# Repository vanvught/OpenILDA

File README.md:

---> WORK IN PROGRESS <---

OpenILDA
========

Cheap ILDA SPI DAC board for Raspberry Pi. 

ILDA output: balanced X/Y - 12 bit,  balanced R/G/B/I - 8 bit.

Playback of ILDA files from external SD card.

OSC support (using RPi <- UART/USB -> PC[java] <- UDP-> iPad/iPod)

This OpenILDA DAC board uses the SPI interface for controlling 3 DAC's. The MCP49x2 device is a dual channel DAC.
As the RPi just has 2 SPI chip enable lines, the DAC /CS lines are created by using a HC139 See viewtopic.php?p=333992#p333992

Of course, I could have used a 12-bit 8-channel DAC (for example TLV5610IDW). This would create less components. However, such a DAC is relatively expensive (24 Euro) and it would have a SO-20 package.

I will post the OpenILDA sd-card player with OSC support (written for bare-metal) soon.

What's next? ()
*. Reduce the amount of OPAMP's (from 6 to 3)
*. Enable using single voltage power supply
	- Use DC/DC converter for -12 volt / +12 volt
	- Use 7805 for 5 volt output voltage
	
See also http://www.raspberrypi.org/phpBB3/viewtopic.php?p=366647#p366647

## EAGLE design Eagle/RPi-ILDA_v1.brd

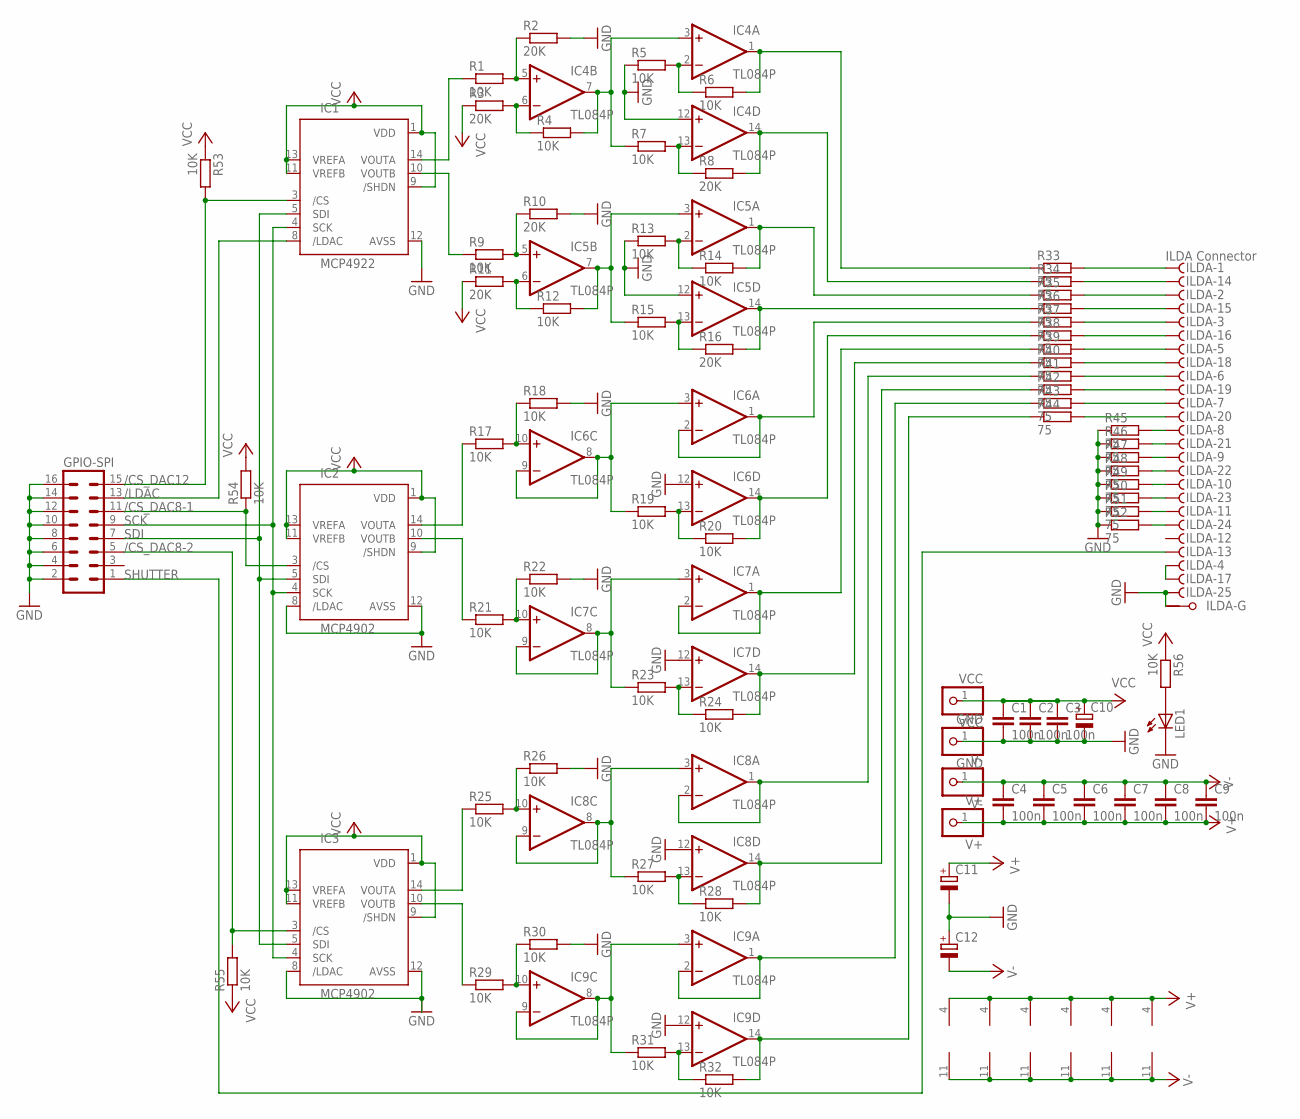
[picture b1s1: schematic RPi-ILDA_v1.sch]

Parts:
C1, C2, C3, C4, C5, C6, C7, C8, C9: 100n; C050-024X044
C10, C11, C12: CPOL-EUE5-6; E5-6
GND: GND; 1X01
GPIO-SPI: MA08-2
IC1: MCP4922; DIL14
IC2, IC3: MCP4902; DIL14
IC4, IC5, IC6, IC7, IC8, IC9: TL084P; DIL14
ILDA: ILDA Connector; F25HP
LED1: LED3MM
R1, R7, R9, R15, R17, R21, R22, R25, R29, R30, R53, R54, R55: 10K; 0204/5
R2, R8, R10, R16: 20K; 0204V
R3, R11: 20K; 0204/5
R4, R5, R6, R12, R13, R14, R18, R19, R20, R23, R24, R26, R27, R28, R31, R32, R56: 10K; 0204V
R33, R34, R35, R36, R37, R38, R39, R40, R41, R42, R43, R44, R45, R46, R47, R48, R49, R50, R51, R52: 75; 0204V
V+: V+; 1X01
V-: V-; 1X01
VCC: VCC; 1X01

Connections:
/CS_DAC8-1: GPIO-SPI.11, IC2.3 (/CS), R54.1
/CS_DAC8-2: GPIO-SPI.5, IC3.3 (/CS), R55.2
/CS_DAC12: GPIO-SPI.15, IC1.3 (/CS), R53.2
/LDAC: GPIO-SPI.13, IC1.8 (/LDAC)
GND: C1.2, C2.2, C3.2, C10.-, C11.-, C12.+, GND.1, GPIO-SPI.2, GPIO-SPI.4, GPIO-SPI.6, GPIO-SPI.8, GPIO-SPI.10, GPIO-SPI.12, GPIO-SPI.14, GPIO-SPI.16, IC1.12 (AVSS), IC2.8 (/LDAC), IC2.12 (AVSS), IC3.8 (/LDAC), IC3.12 (AVSS), IC4.12 (+IN), IC5.12 (+IN), IC6.12 (+IN), IC7.12 (+IN), IC8.12 (+IN), IC9.12 (+IN), ILDA.25 (F), ILDA.G1, LED1.K (C), R2.2, R5.1, R10.2, R13.1, R18.2, R22.2, R26.2, R30.2, R45.1, R46.1, R47.1, R48.1, R49.1, R50.1, R51.1, R52.1
unnamed: LED1.A, R56.2
unnamed: ILDA.3 (F), R37.2
unnamed: IC4.2 (-IN), R5.2, R6.1
unnamed: IC5.2 (-IN), R13.2, R14.1
unnamed: IC5.13 (-IN), R15.2, R16.1
unnamed: IC3.14 (VOUTA), R25.1
unnamed: IC7.14 (OUT), R24.2, R40.1
unnamed: IC7.13 (-IN), R23.2, R24.1
unnamed: IC7.10 (+IN), R21.2, R22.1
unnamed: ILDA.4 (F), ILDA.17 (F)
unnamed: IC7.3 (+IN), IC7.8 (OUT), IC7.9 (-IN), R23.1
unnamed: IC7.1 (OUT), IC7.2 (-IN), R39.1
unnamed: ILDA.5 (F), R39.2
unnamed: IC1.14 (VOUTA), R1.1
unnamed: IC1.10 (VOUTB), R9.1
unnamed: ILDA.18 (F), R40.2
unnamed: IC6.14 (OUT), R20.2, R38.1
unnamed: IC4.13 (-IN), R7.2, R8.1
unnamed: IC6.13 (-IN), R19.2, R20.1
unnamed: IC8.14 (OUT), R28.2, R42.1
unnamed: IC6.10 (+IN), R17.2, R18.1
unnamed: IC6.3 (+IN), IC6.8 (OUT), IC6.9 (-IN), R19.1
unnamed: IC6.1 (OUT), IC6.2 (-IN), R37.1
unnamed: IC8.13 (-IN), R27.2, R28.1
unnamed: IC8.10 (+IN), R25.2, R26.1
unnamed: IC8.3 (+IN), IC8.8 (OUT), IC8.9 (-IN), R27.1
unnamed: IC8.1 (OUT), IC8.2 (-IN), R41.1
unnamed: ILDA.8 (F), R45.2
unnamed: ILDA.6 (F), R41.2
unnamed: ILDA.16 (F), R38.2
unnamed: IC5.14 (OUT), R16.2, R36.1
unnamed: ILDA.19 (F), R42.2
unnamed: IC5.1 (OUT), R14.2, R35.1
unnamed: IC9.14 (OUT), R32.2, R44.1
unnamed: IC9.13 (-IN), R31.2, R32.1
unnamed: IC9.10 (+IN), R29.2, R30.1
unnamed: IC9.3 (+IN), IC9.8 (OUT), IC9.9 (-IN), R31.1
unnamed: IC9.1 (OUT), IC9.2 (-IN), R43.1
unnamed: IC3.10 (VOUTB), R29.1
unnamed: IC4.14 (OUT), R8.2, R34.1
unnamed: IC4.1 (OUT), R6.2, R33.1
unnamed: IC5.3 (+IN), IC5.7 (OUT), R12.2, R15.1
unnamed: IC4.6 (-IN), R3.2, R4.1
unnamed: IC5.6 (-IN), R11.2, R12.1
unnamed: ILDA.7 (F), R43.2
unnamed: ILDA.20 (F), R44.2
unnamed: ILDA.21 (F), R46.2
unnamed: ILDA.9 (F), R47.2
unnamed: ILDA.22 (F), R48.2
unnamed: ILDA.10 (F), R49.2
unnamed: ILDA.23 (F), R50.2
unnamed: IC2.14 (VOUTA), R17.1
unnamed: ILDA.11 (F), R51.2
unnamed: ILDA.24 (F), R52.2
unnamed: IC2.10 (VOUTB), R21.1
unnamed: IC5.5 (+IN), R9.2, R10.1
unnamed: IC4.5 (+IN), R1.2, R2.1
unnamed: IC4.3 (+IN), IC4.7 (OUT), R4.2, R7.1
unnamed: ILDA.1 (F), R33.2
unnamed: ILDA.14 (F), R34.2
unnamed: ILDA.15 (F), R36.2
unnamed: ILDA.2 (F), R35.2
SCK: GPIO-SPI.9, IC1.4 (SCK), IC2.4 (SCK), IC3.4 (SCK)
SDI: GPIO-SPI.7, IC1.5 (SDI), IC2.5 (SDI), IC3.5 (SDI)
SHUTTER: GPIO-SPI.1, ILDA.13 (F)
V+: C4.2, C5.2, C6.2, C7.2, C8.2, C9.2, C11.+, IC4.4 (V+), IC5.4 (V+), IC6.4 (V+), IC7.4 (V+), IC8.4 (V+), IC9.4 (V+), V+.1
V-: C4.1, C5.1, C6.1, C7.1, C8.1, C9.1, C12.-, IC4.11 (V-), IC5.11 (V-), IC6.11 (V-), IC7.11 (V-), IC8.11 (V-), IC9.11 (V-), V-.1
VCC: C1.1, C2.1, C3.1, C10.+, IC1.1 (VDD), IC1.9 (/SHDN), IC1.11 (VREFB), IC1.13 (VREFA), IC2.1 (VDD), IC2.9 (/SHDN), IC2.11 (VREFB), IC2.13 (VREFA), IC3.1 (VDD), IC3.9 (/SHDN), IC3.11 (VREFB), IC3.13 (VREFA), R3.1, R11.1, R53.1, R54.2, R55.1, R56.1, VCC.1

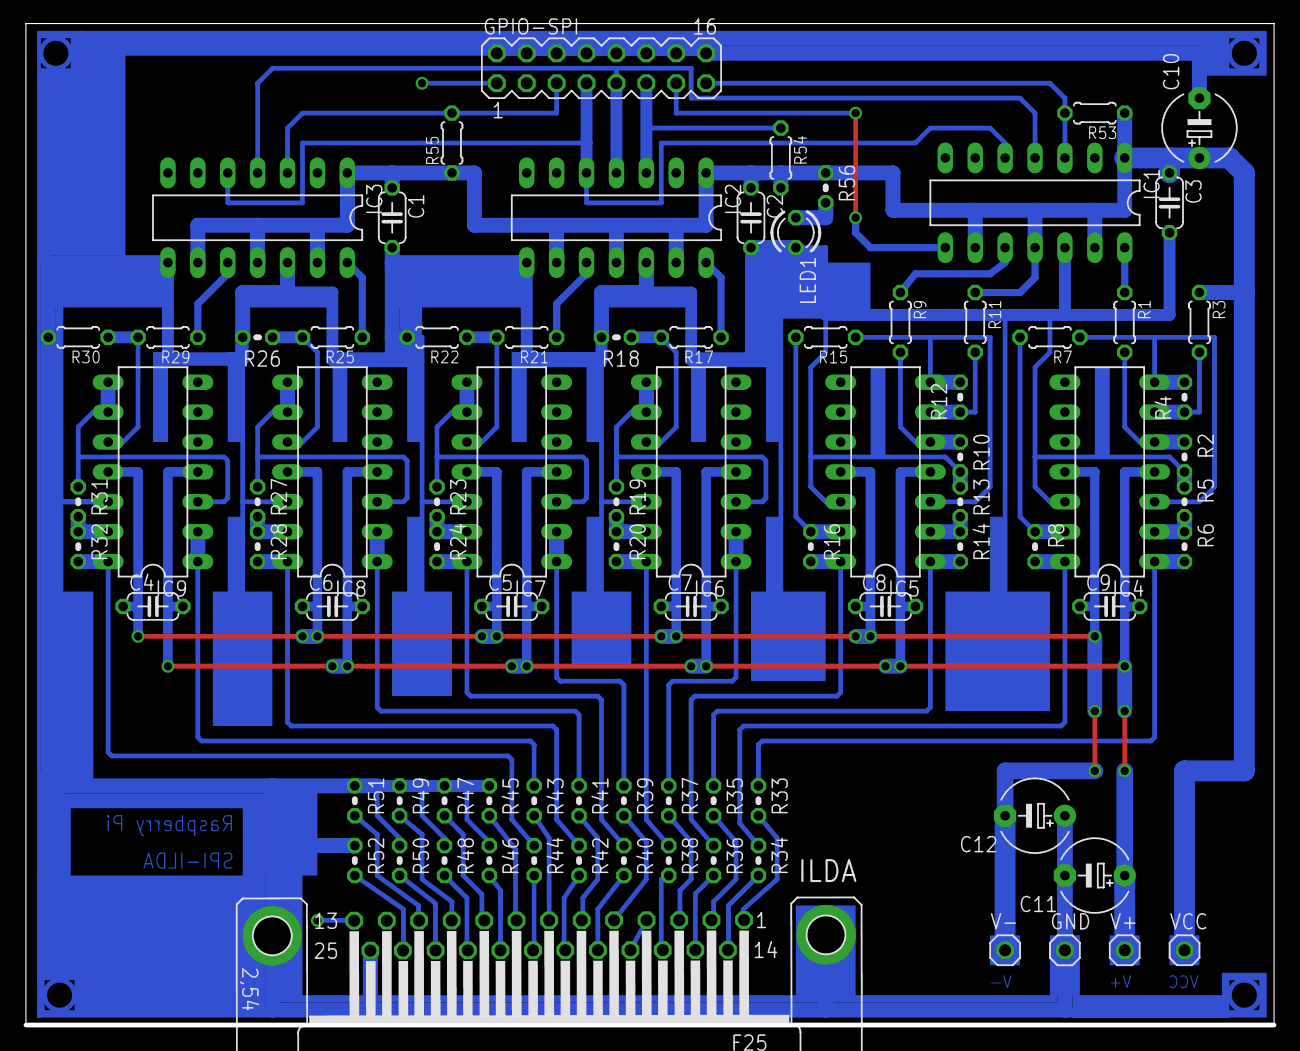
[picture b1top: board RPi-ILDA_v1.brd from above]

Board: 2 copper layers, 106.0 x 85.1 mm, 84 parts (0 on the bottom side), 73 nets.

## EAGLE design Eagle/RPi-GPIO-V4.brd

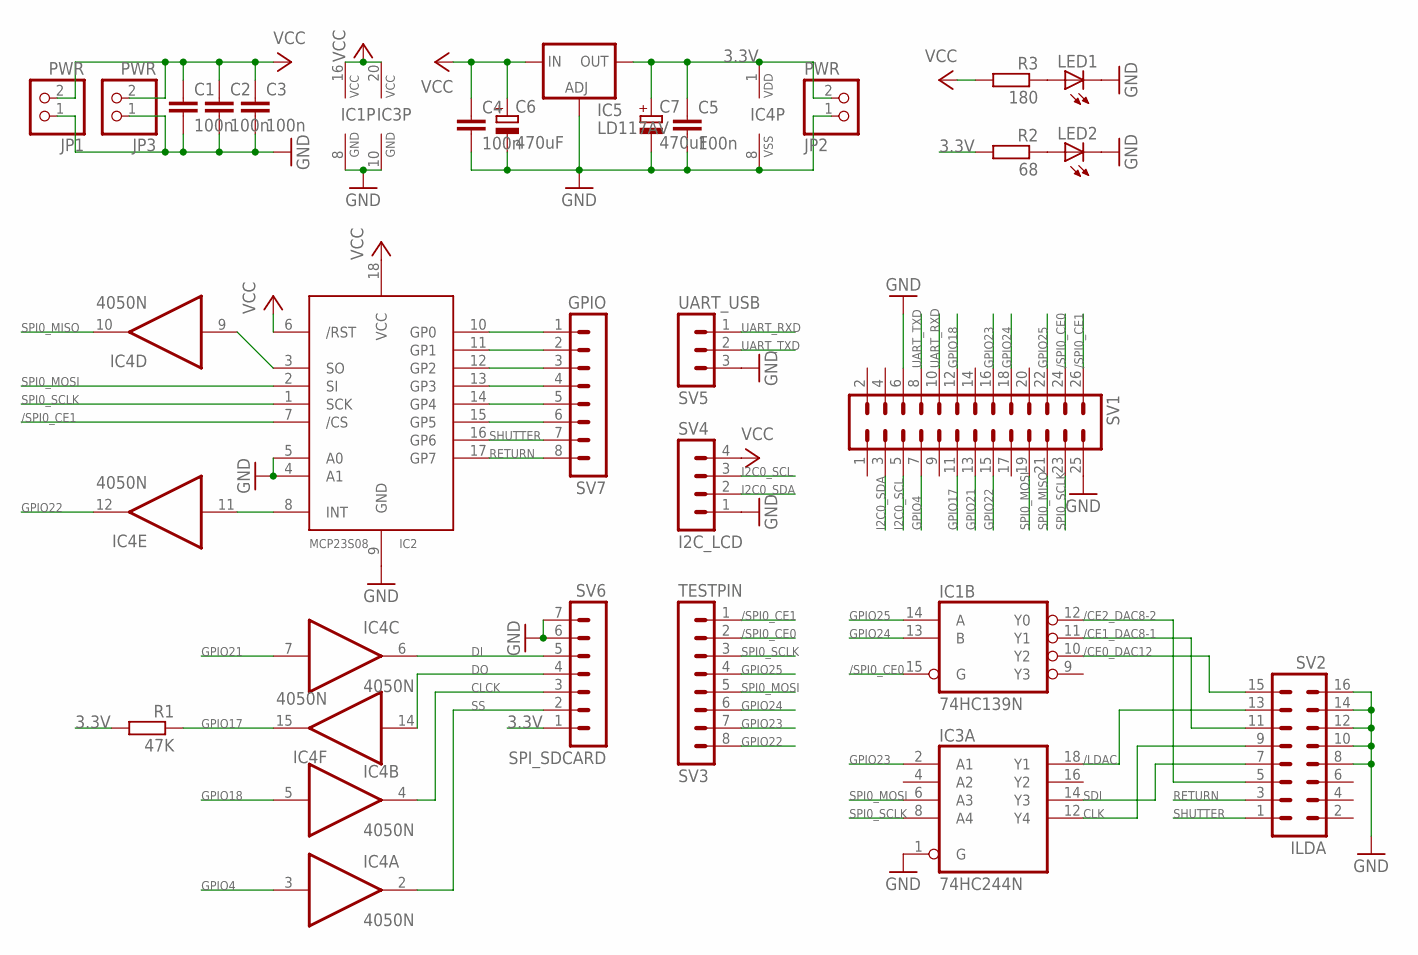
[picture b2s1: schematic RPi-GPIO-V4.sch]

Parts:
C1, C2, C3, C4, C5: 100n; C050-024X044
C6, C7: 470uF; E5-8,5
IC1: 74HC139N; DIL16
IC2: MCP2300X/P; DIL18
IC3: 74HC244N; DIL20
IC4: 4050N; DIL16
IC5: LD117AV; TO220L1
JP1, JP2, JP3: PWR; 1X02
LED1, LED2: LED3MM
R1: 47K; 0204/5
R2: 68; 0204/5
R3: 180; 0204/5
SV1: MA13-2
SV2: ILDA; MA08-2
SV3: TESTPIN; MA08-1
SV4: I2C_LCD; MA04-1
SV5: UART_USB; MA03-1
SV6: SPI_SDCARD; MA07-1
SV7: GPIO; MA08-1

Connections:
3.3V: C5.1, C7.+, IC4.1 (VDD), IC5.2 (OUT), JP2.2, R1.2, R2.2, SV6.1
/CE0_DAC12: IC1.10 (Y2), SV2.15
/CE1_DAC8-1: IC1.11 (Y1), SV2.11
/CE2_DAC8-2: IC1.12 (Y0), SV2.5
/LDAC: IC3.18 (Y1), SV2.13
/SPI0_CE0: IC1.15 (G), SV1.24, SV3.2
/SPI0_CE1: IC2.7 (/CS), SV1.26, SV3.1
CLCK: IC4.4 (O), SV6.3
CLK: IC3.12 (Y4), SV2.9
DI: IC4.6 (O), SV6.5
DO: IC4.14 (I), SV6.4
GND: C1.2, C2.2, C3.2, C4.2, C5.2, C6.-, C7.-, IC1.8 (GND), IC2.4 (A1), IC2.5 (A0), IC2.9 (GND), IC3.1 (G), IC3.10 (GND), IC4.8 (VSS), IC5.1 (ADJ), JP1.1, JP2.1, JP3.1, LED1.K (C), LED2.K (C), SV1.6, SV1.25, SV2.8, SV2.10, SV2.12, SV2.14, SV2.16, SV4.1, SV5.3, SV6.6, SV6.7
GPIO4: IC4.3 (I), SV1.7
GPIO17: IC4.15 (O), R1.1, SV1.11
GPIO18: IC4.5 (I), SV1.12
GPIO21: IC4.7 (I), SV1.13
GPIO22: IC4.12 (O), SV1.15, SV3.8
GPIO23: IC3.2 (A1), SV1.16, SV3.7
GPIO24: IC1.13 (B), SV1.18, SV3.6
GPIO25: IC1.14 (A), SV1.22, SV3.4
I2C0_SCL: SV1.5, SV4.3
I2C0_SDA: SV1.3, SV4.2
unnamed: LED1.A, R3.1
unnamed: LED2.A, R2.1
unnamed: IC2.3 (SO), IC4.9 (I)
unnamed: IC2.10 (GP0), SV7.1
unnamed: IC2.11 (GP1), SV7.2
unnamed: IC2.12 (GP2), SV7.3
unnamed: IC2.13 (GP3), SV7.4
unnamed: IC2.14 (GP4), SV7.5
unnamed: IC2.15 (GP5), SV7.6
unnamed: IC2.8 (INT), IC4.11 (I)
RETURN: IC2.17 (GP7), SV2.3, SV7.8
SDI: IC3.14 (Y3), SV2.7
SHUTTER: IC2.16 (GP6), SV2.1, SV7.7
SPI0_MISO: IC4.10 (O), SV1.21
SPI0_MOSI: IC2.2 (SI), IC3.6 (A3), SV1.19, SV3.5
SPI0_SCLK: IC2.1 (SCK), IC3.8 (A4), SV1.23, SV3.3
SS: IC4.2 (O), SV6.2
UART_RXD: SV1.10, SV5.1
UART_TXD: SV1.8, SV5.2
VCC: C1.1, C2.1, C3.1, C4.1, C6.+, IC1.16 (VCC), IC2.6 (/RST), IC2.18 (VCC), IC3.20 (VCC), IC5.3 (IN), JP1.2, JP3.2, R3.2, SV4.4

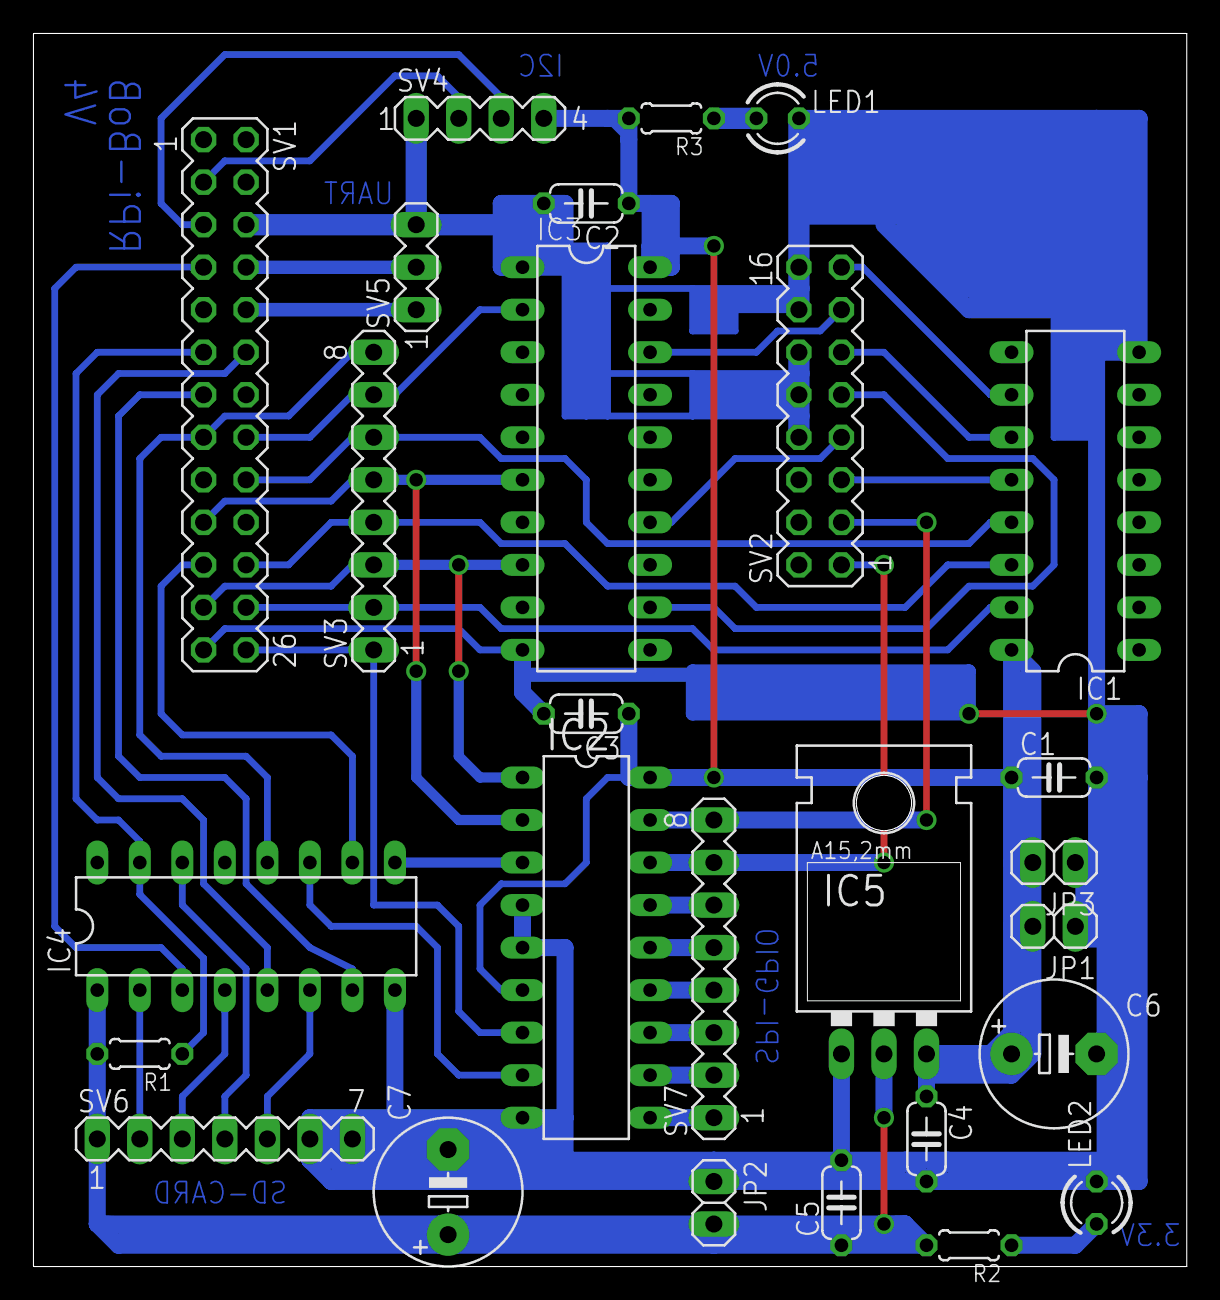
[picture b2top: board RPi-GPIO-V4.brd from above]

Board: 2 copper layers, 68.9 x 73.7 mm, 27 parts (0 on the bottom side), 42 nets.

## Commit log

2013-06-29 Initial load
2013-06-29 Function 'hang' moved downwards
2013-07-11 Removed bcm2835_spi_mcp49x2 prototypes
2013-07-11 Loop 'halt' added
2013-07-11 Added 'inline' for bcm2835_spi_setBitOrder
2013-12-23 Function mcp7941x_set_date_time added
2013-12-23 Update RTC from Linux time added
2013-12-23 bug fix
2013-12-27 Support added for BitWizard UI
2013-12-27 i2c routine NACK reset
2013-12-27 minor bug fix
2013-12-27 Minor updates
2013-12-28 Some cleanup
2013-12-28 OpenILDA standalon ILDA player added
2013-12-28 BitWizard UI support added
2013-12-29 bw_i2c_ui.c updated
2013-12-30 New functions added
2013-12-30 Another cleanup := make it equal to OpenDMX
2014-01-04 bw_i2cdetect added
2014-01-04 Build instructions added
2014-01-04 sys_time.c added
2014-01-05 main.c renamed to i2cdetect.c
2014-01-19 Eagle files added again
2014-01-19 BitWizard multiple same devices support added
2014-01-19 none related Eclipse projects deleted
2014-01-24 PL011 support added
2014-01-26 PL011 support updated
2014-01-29 Project 'sdcard-emmc' refreshed
2014-01-29 Project 'bw_spi_dio-tester-libbob' added
2014-01-29 Project 'mcp23s08-tester-libbob' added
2014-01-29 uwait.S added
2014-01-29 Updated with newlib-2.1.0
2014-01-29 uwait function removed
2014-01-29 Minor cleanup
2014-01-31 MailBox support added
2014-01-31 Displaying (EMMC, UART, ARM, CORE) clock rates
2014-02-02 _USE_STRFUNC 2
2014-02-03 License statement added
2014-02-08 Library 'hal' added
2014-02-08 Project 'firmware' deleted
2014-02-09 bcm2835_wdog.c added
2014-02-10 Minor cleanup bw_ header files
2014-02-22 Minor cleanup header files
2014-03-01 BitWizard spi_7fets support added
2014-03-04 Minor update for FUNC bcm2835_spi_write
2014-03-12 Updates for firmware
2014-10-24 Doxygen
2014-10-24 Matrix added
2014-10-26 Identifying the Device bug fixed
2014-10-26 Some minor cleanup
2014-11-01 "const" added where possible
2014-11-02 Added all BW devices
2014-11-02 New project added
2014-11-03 Function newline() improved
2014-11-03 BitWizard i2c_dio support added
2014-11-03 BitWizard spi_relay support added
2014-11-07 Renamed function uwait() to udelay()
2014-11-11 bcm2835.c / .h split
2014-11-12 .h files cleanup
2014-11-15 Some more cleanup
2014-11-15 Another cleanup
2014-11-15 Added BCM2835_EMMC_TypeDef
2014-11-15 Added bcm2835_led.h
2014-11-17 Added files bcm2835_pl011_dmx512.c / .h
2014-11-23 Updated bcm2835_emmc.h, added empty bcm2835_emmc.c
2014-11-30 Major cleanup
2014-11-30 BitWizard spi_dimmer support added
2014-12-27 Preparing for AVR
2014-12-27 Minor changes
2014-12-29 Optimized for AVR
2014-12-29 Ready for AVR
2014-12-29 README update
2014-12-31 Updated for AVR
2014-12-31 get functions added
    bw_spi_lcd_get_backlight
    bw_spi_lcd_get_contrast
2014-12-31 More Doxygen
2014-12-31 Update for AVR
2015-01-01 Minor cleanup for I2C SlaveAddress
2015-01-01 Work in progress
2015-01-01 Changed clock divider / wait time
2015-01-01 Added all include files from project bob
2015-01-02 Doxgen
2015-01-03 Project hal renamed to bob-baremetal
2015-01-03 Added mini_uart.c
2015-01-03 Added project firmware
2015-01-03 Moving functions to its own .c file
2015-01-04 Rewritten
2015-01-04 Deleted lib folder
2015-01-05 Major
2015-01-05 Added project sdcard-emmc-libff9b
2015-01-13 Added RGB color definitions
2015-01-23 Upgrade Eclipse to Luna
2015-02-11 Minor change
2015-06-15 Major code updates
2015-07-02 splint
2015-07-05 Multiple updates
2015-07-07 L1 cache enabled
2015-07-10 Optimized for 800 x 480
    For example
    https://www.kiwi-electronics.nl/hdmi-7-inch-800x480-display-backpack-met-touchscreen
2015-07-11 Support for Raspberry Pi 2
2015-07-11 Support for Raspberry Pi Model 2B
2015-07-18 Added vprintf embedded implementation
2015-08-07 Clean up
2015-08-26 Completely rewritten
2015-08-28 Added support for caching
2015-08-29 Removed "memmove"
2015-08-31 Minor code clean up
2016-02-27 Copyright update
2016-06-26 sync with https://github.com/vanvught/rpidmx512
